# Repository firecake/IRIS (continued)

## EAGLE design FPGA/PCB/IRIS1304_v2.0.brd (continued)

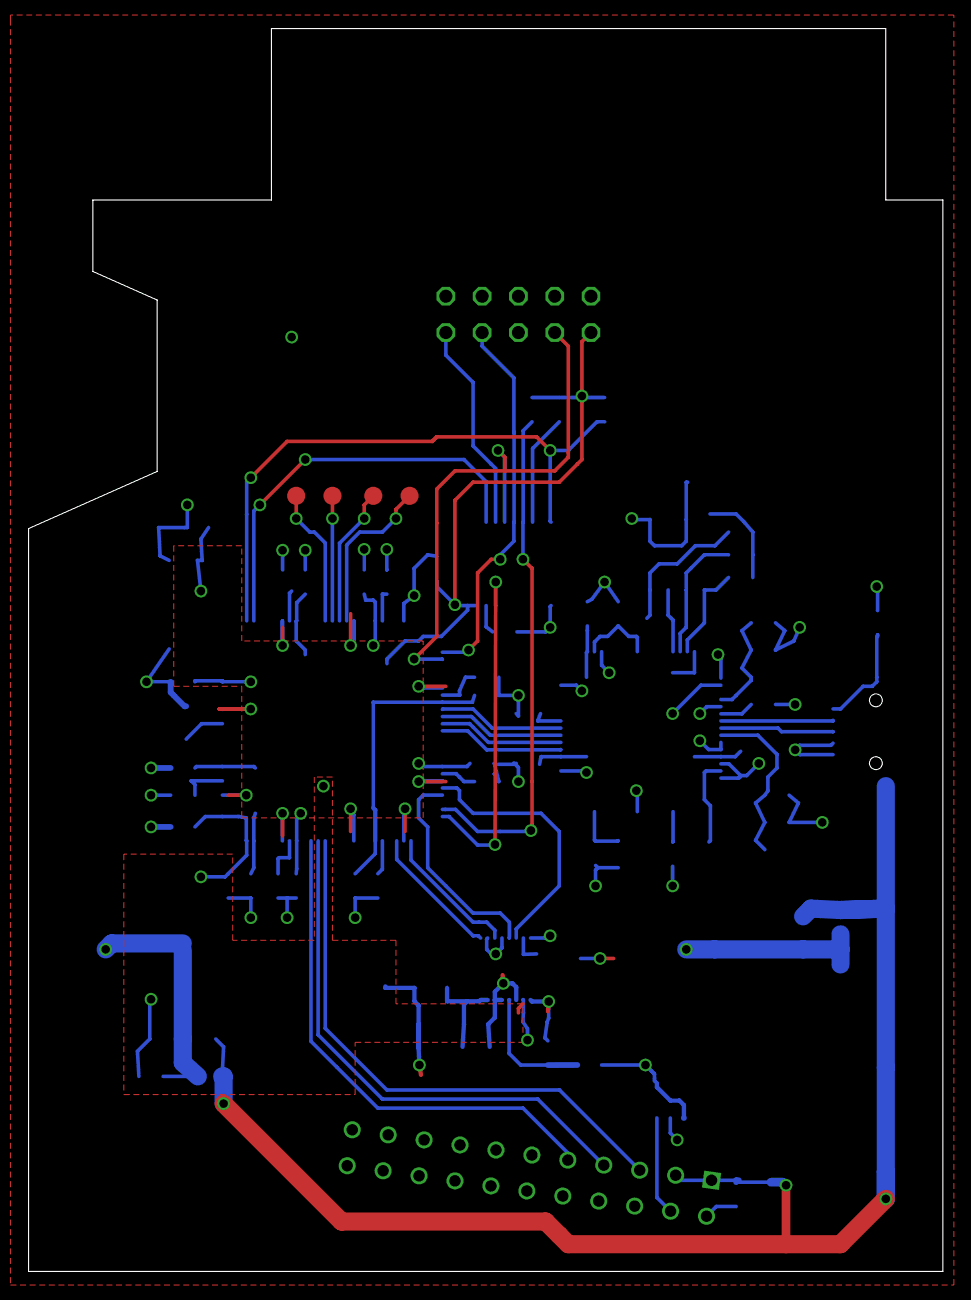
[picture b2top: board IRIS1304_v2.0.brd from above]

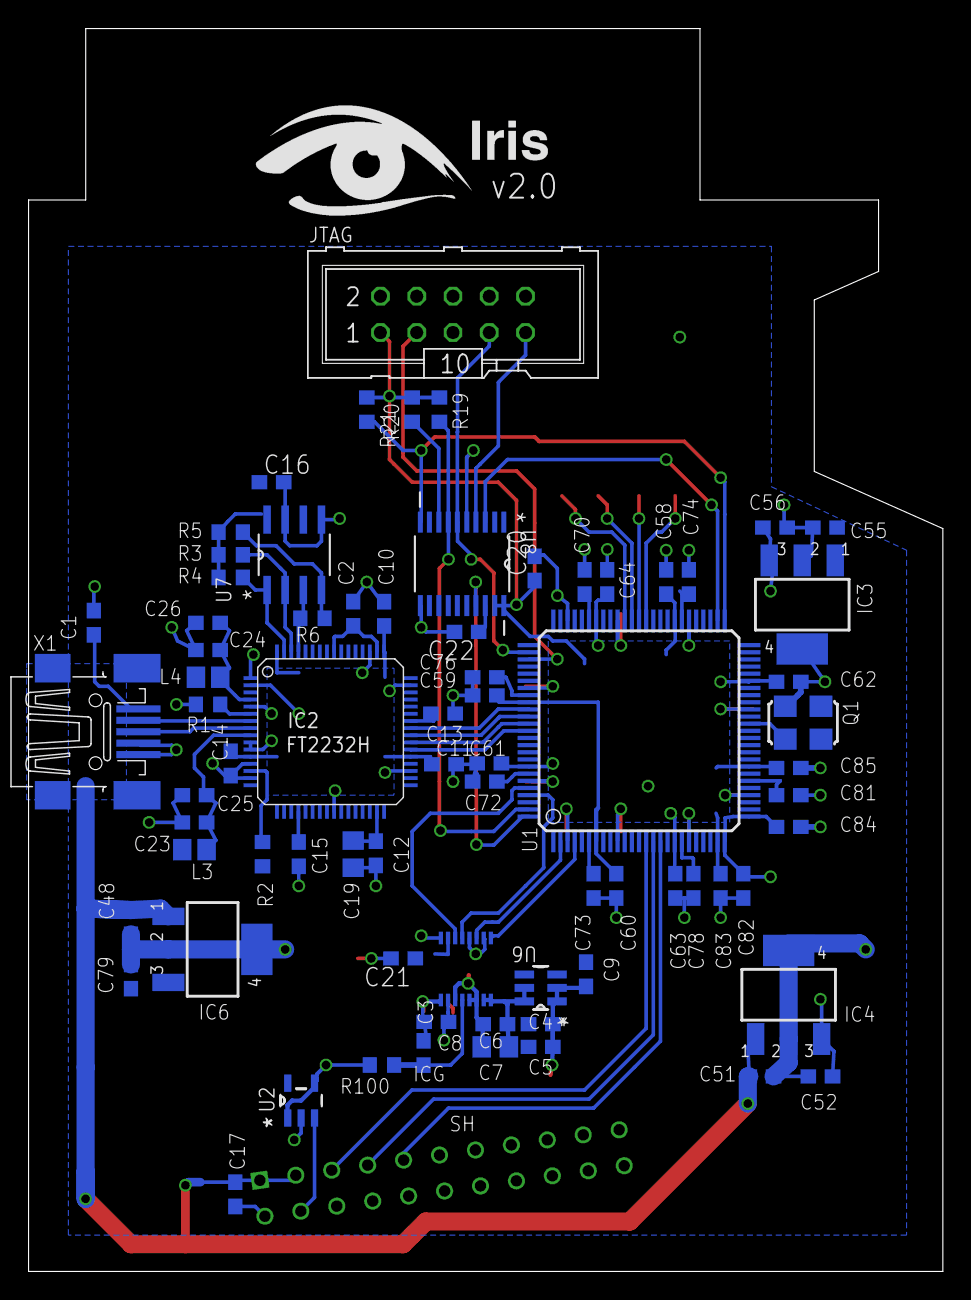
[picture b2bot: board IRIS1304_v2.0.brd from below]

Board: 2 copper layers, 64.0 x 87.0 mm, 79 parts (74 on the bottom side), 44 nets.

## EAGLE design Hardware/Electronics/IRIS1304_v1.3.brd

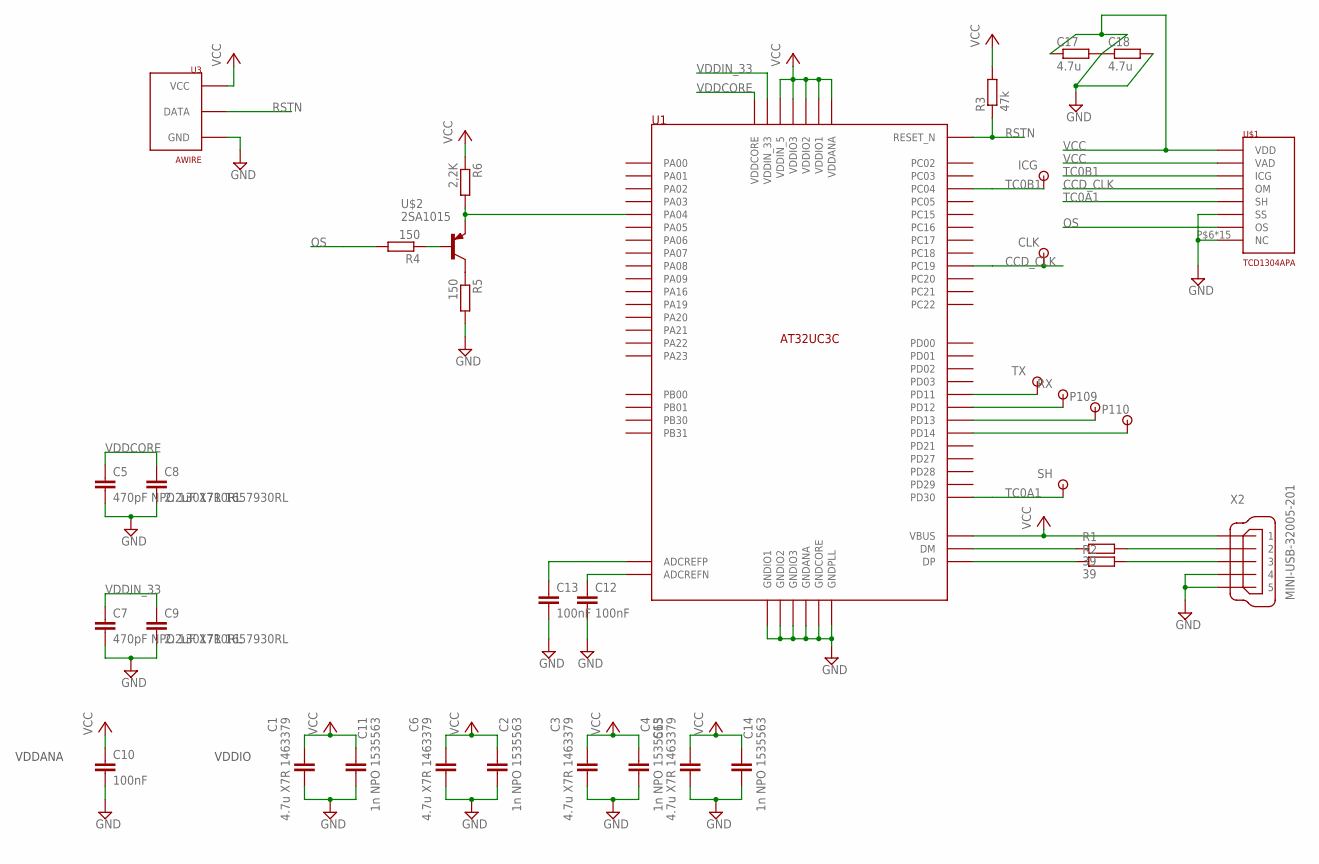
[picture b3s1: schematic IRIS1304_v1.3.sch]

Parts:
C1, C3, C6, C15: 4.7u X7R 1463379; C0603; MPN 0201YC101KAT2A
C2, C4, C11, C14: 1n NPO 1535563; C0402
C5, C7: 470pF NPO 1301710RL; C0603
C8, C9: 2.2uF X7R 1657930RL; C0603
C10, C12, C13: 100nF; C0603
C17, C18: 4.7u; R0603
CLK: TP
ICG: TP
P109, P110: TP
R1, R2: 39; R0603
R3: 47k; R0603
R4: 150; R0603
R5: 150; M0805
R6: 2,2K; R0603
RX: TP
SH: TP
TX: TP
U1: AT32UC3C; TQFP64
U3: AWIRE
U$1: TCD1304APA; ILX511
U$2: 2SA1015; SOT23
X2: MINI-USB-32005-201; 32005-201

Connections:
CCD_CLK: CLK.P$1, U1.P$43 (PC19), U$1.P$4 (OM)
GND: C1.2, C2.2, C3.2, C4.2, C5.2, C6.2, C7.2, C8.2, C9.2, C10.2, C11.2, C12.2, C13.2, C14.2, C15.2, C17.2, C18.2, R5.2, U1.P$6 (GNDIO1), U1.P$17 (GNDANA), U1.P$26 (GNDPLL), U1.P$30 (GNDCORE), U1.P$36 (GNDIO2), U1.P$52 (GNDIO3), U3.P$3 (GND), U$1.P$6 (NC), U$1.P$7 (NC), U$1.P$8 (NC), U$1.P$9 (NC), U$1.P$10 (NC), U$1.P$11 (NC), U$1.P$12 (NC), U$1.P$13 (NC), U$1.P$14 (NC), U$1.P$15 (NC), U$1.P$16 (NC), U$1.P$17 (NC), U$1.P$18 (NC), U$1.P$19 (NC), U$1.P$20 (NC), U$1.P$22 (SS), X2.4, X2.5
unnamed: R1.1, U1.P$24 (DM)
unnamed: R2.1, U1.P$25 (DP)
unnamed: R1.2, X2.2
unnamed: R2.2, X2.3
unnamed: R6.2, U1.P$7 (PA04), U$2.2 (E)
unnamed: C13.1, U1.P$14 (ADCREFP)
unnamed: R5.1, U$2.3 (C)
unnamed: R4.1, U$2.1 (B)
unnamed: C12.1, U1.P$15 (ADCREFN)
unnamed: P109.P$1, U1.P$55 (PD13)
unnamed: RX.P$1, U1.P$54 (PD12)
unnamed: P110.P$1, U1.P$56 (PD14)
unnamed: TX.P$1, U1.P$53 (PD11)
OS: R4.2, U$1.P$21 (OS)
RSTN: R3.1, U1.P$64 (RESET_N), U3.P$2 (DATA)
TC0A1: SH.P$1, U1.P$61 (PD30), U$1.P$5 (SH)
TC0B1: ICG.P$1, U1.P$37 (PC04), U$1.P$3 (ICG)
VCC: C1.1, C2.1, C3.1, C4.1, C6.1, C10.1, C11.1, C14.1, C15.1, C17.1, C18.1, R3.2, R6.1, U1.P$5 (VDDIO1), U1.P$18 (VDDANA), U1.P$23 (VBUS), U1.P$27 (VDDIN_5), U1.P$35 (VDDIO2), U1.P$51 (VDDIO3), U3.P$1 (VCC), U$1.P$1 (VDD), U$1.P$2 (VAD), X2.1
VDDCORE: C5.1, C8.1, U1.P$29 (VDDCORE)
VDDIN_33: C7.1, C9.1, U1.P$28 (VDDIN_33)

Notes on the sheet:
VDDIO
VDDANA

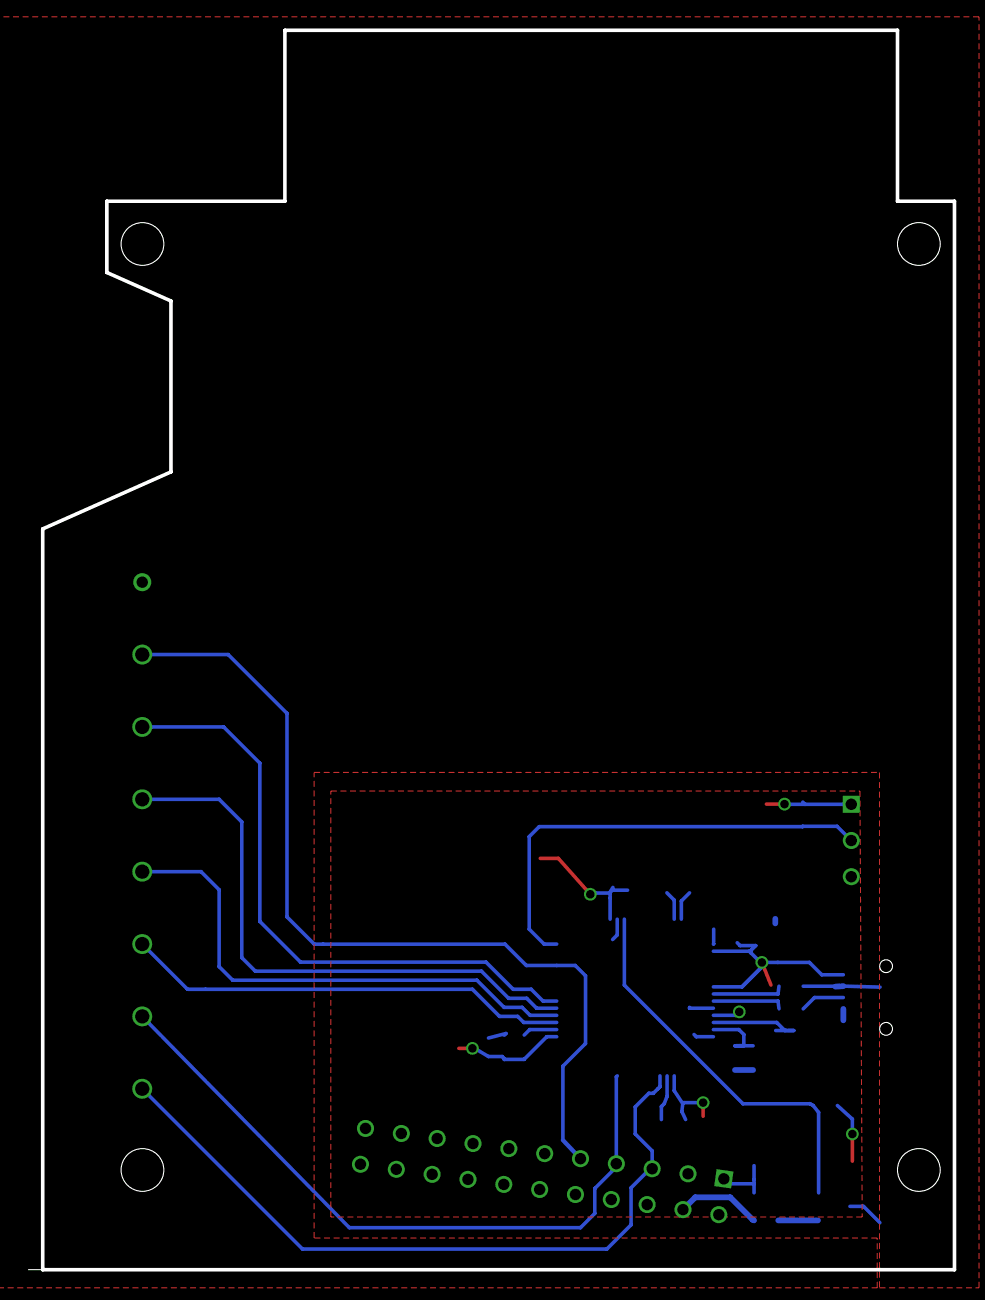
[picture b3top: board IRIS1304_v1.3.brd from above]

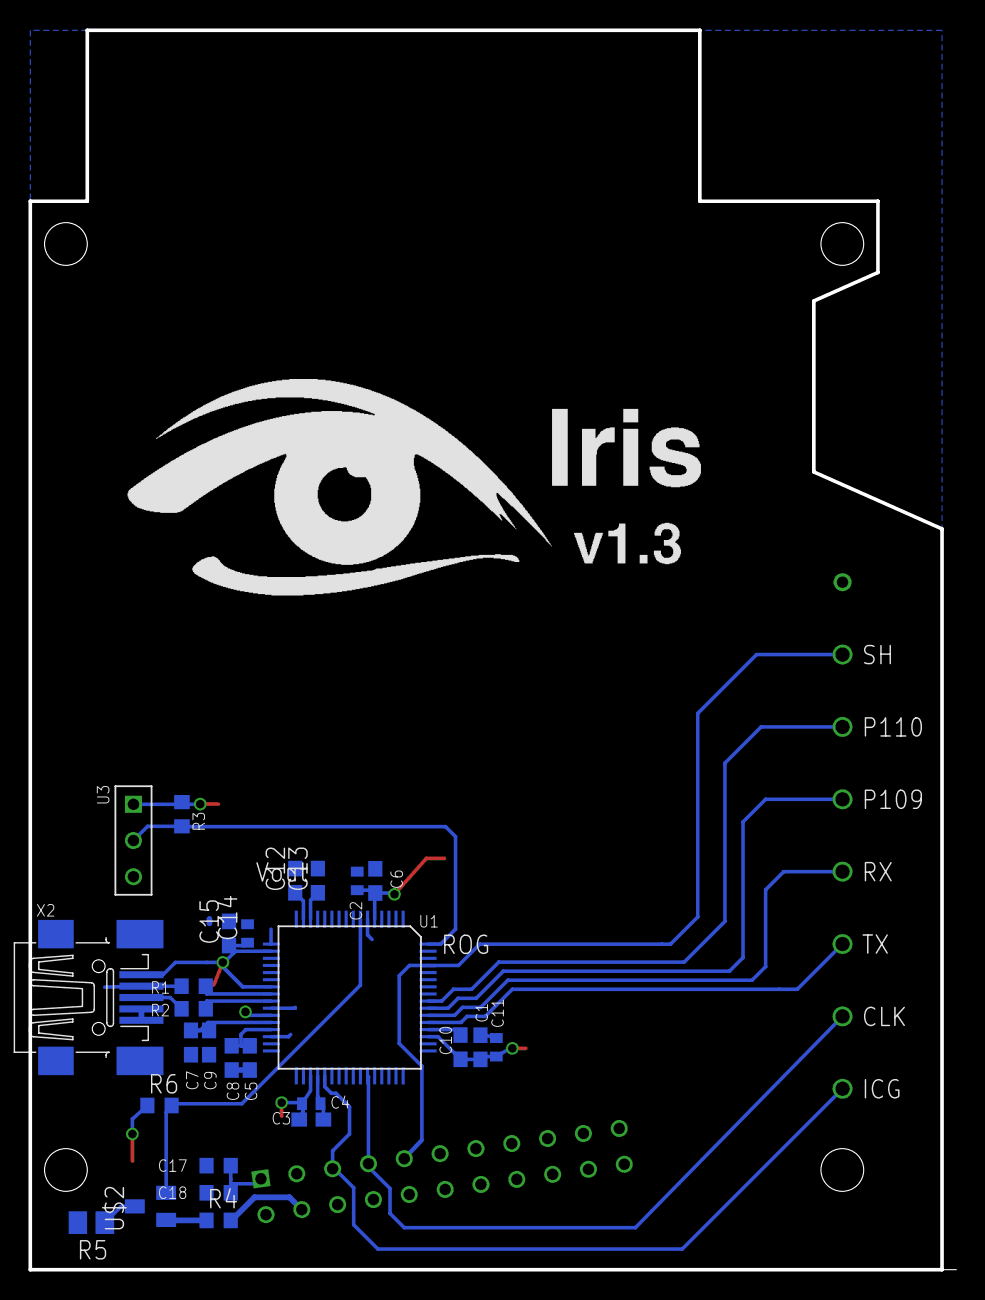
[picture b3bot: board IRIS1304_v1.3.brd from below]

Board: 2 copper layers, 65.0 x 87.0 mm, 35 parts (34 on the bottom side), 22 nets.

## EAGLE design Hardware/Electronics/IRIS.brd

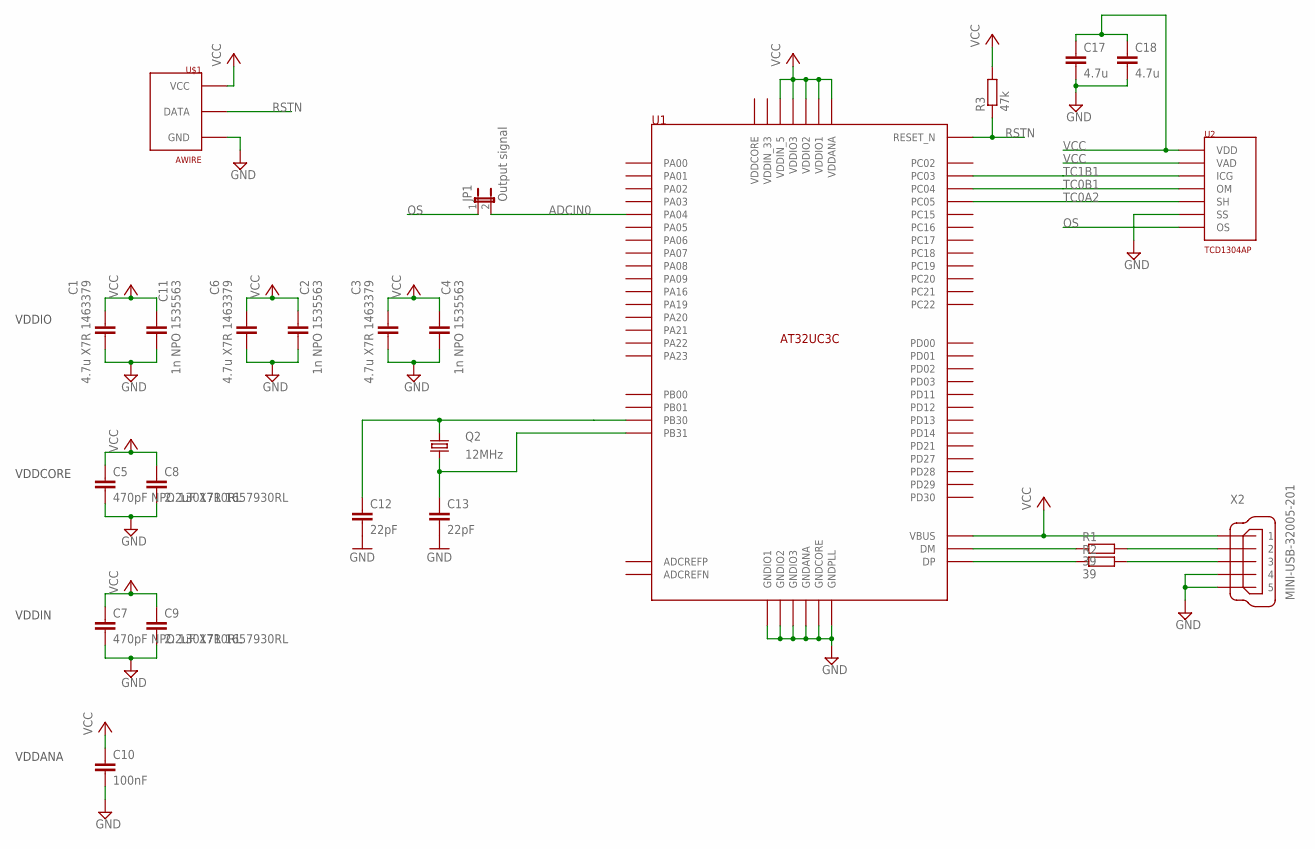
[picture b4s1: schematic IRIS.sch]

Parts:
C1, C3, C6: 4.7u X7R 1463379; C0603
C2, C4, C11: 1n NPO 1535563; C0402
C5, C7: 470pF NPO 1301710RL; C0603
C8, C9: 2.2uF X7R 1657930RL; C0603
C10: 100nF; C0603
C12, C13: 22pF; C0402
C17, C18: 4.7u; C0805
JP1: Output signal; JP1
Q2: 12MHz; CRYSTAL-SMD-5X3
R1, R2: 39; R0603
R3: 47k; R0603
U1: AT32UC3C; TQFP64
U2: TCD1304AP
U$1: AWIRE
X2: MINI-USB-32005-201; 32005-201

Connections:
ADCIN0: JP1.2, U1.P$7 (PA04)
GND: C1.2, C2.2, C3.2, C4.2, C5.2, C6.2, C7.2, C8.2, C9.2, C10.2, C11.2, C12.2, C13.2, C17.2, C18.2, U1.P$6 (GNDIO1), U1.P$17 (GNDANA), U1.P$26 (GNDPLL), U1.P$30 (GNDCORE), U1.P$36 (GNDIO2), U1.P$52 (GNDIO3), U2.P$22 (SS), U$1.P$3 (GND), X2.4, X2.5; also elsewhere on the board
unnamed: R1.1, U1.P$24 (DM)
unnamed: R2.1, U1.P$25 (DP)
unnamed: R1.2, X2.2
unnamed: R2.2, X2.3
unnamed: C12.1, Q2.3 (2), U1.P$31 (PB30)
unnamed: C13.1, Q2.1, U1.P$32 (PB31)
OS: JP1.1, U2.P$21 (OS)
RSTN: R3.1, U1.P$64 (RESET_N), U$1.P$2 (DATA); also elsewhere on the board
TC0A2: U1.P$38 (PC05), U2.P$5 (SH)
TC0B1: U1.P$37 (PC04), U2.P$4 (OM)
TC1B1: U1.P$34 (PC03), U2.P$3 (ICG)
VCC: C1.1, C2.1, C3.1, C4.1, C5.1, C6.1, C7.1, C8.1, C9.1, C10.1, C11.1, C17.1, C18.1, R3.2, U1.P$5 (VDDIO1), U1.P$18 (VDDANA), U1.P$23 (VBUS), U1.P$27 (VDDIN_5), U1.P$35 (VDDIO2), U1.P$51 (VDDIO3), U2.P$1 (VDD), U2.P$2 (VAD), U$1.P$1 (VCC), X2.1; also elsewhere on the board

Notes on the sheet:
VDDCORE
VDDIN
VDDIO
VDDANA

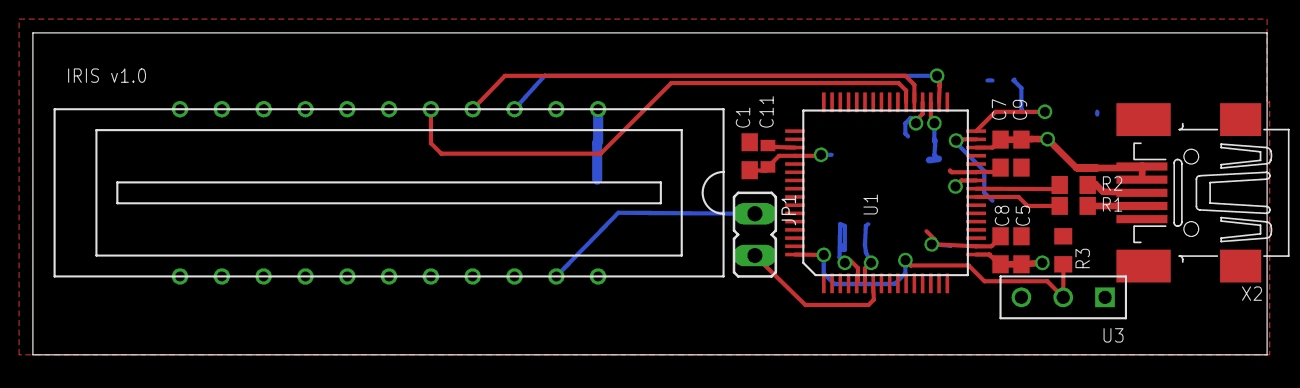
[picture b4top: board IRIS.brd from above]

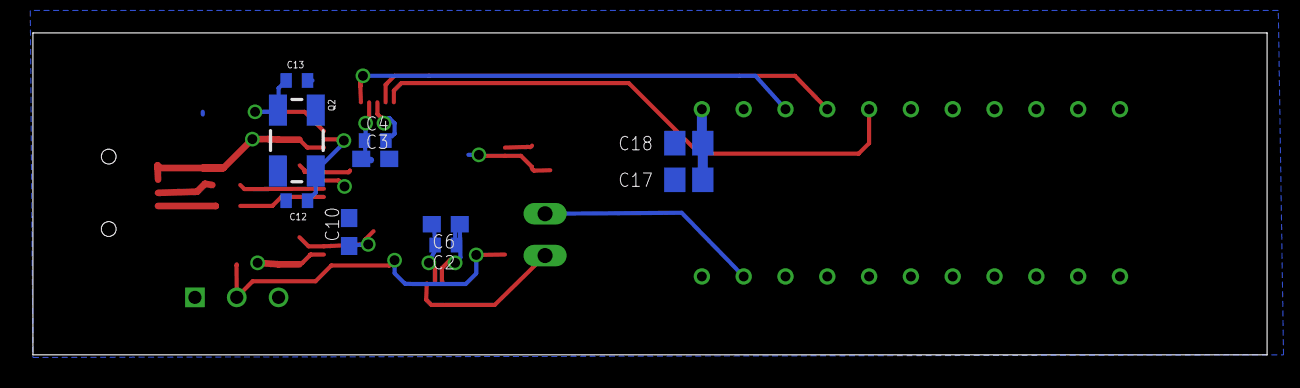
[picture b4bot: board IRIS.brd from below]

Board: 2 copper layers, 75.0 x 19.6 mm, 24 parts (10 on the bottom side), 14 nets.

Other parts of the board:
U3: AWIRE

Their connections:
GND: U3.P$3; also elsewhere on the board
RSTN: U3.P$2; also elsewhere on the board
VCC: U3.P$1; also elsewhere on the board

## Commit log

2012-08-29 Initial project structure
2012-08-29 Added license files
2012-08-29 Some schematic modifications…
2012-08-29 Schematic modifications…
2012-08-29 Board routed.
2012-08-30 First candidate for v1.0
2012-09-04 First version
2014-08-06 second commit...
2014-09-13 First commit after release of version 1.3
2015-04-30 Correct some bugs...
2015-05-02 First vcdl release
2015-05-22 RC1
    Rc1 commit still some bug but not so much…
2015-05-22 Micro version firmware update
2015-06-06 First release
2015-06-07 Unused file deleted...
2015-06-12 v3.0
2015-12-18 Added expansion connectors and EEPROM
